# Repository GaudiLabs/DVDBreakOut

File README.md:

# DVDBreakOut
Simple breakout board to controll the laser and the two coils of an Optical Laser Pickup Unit

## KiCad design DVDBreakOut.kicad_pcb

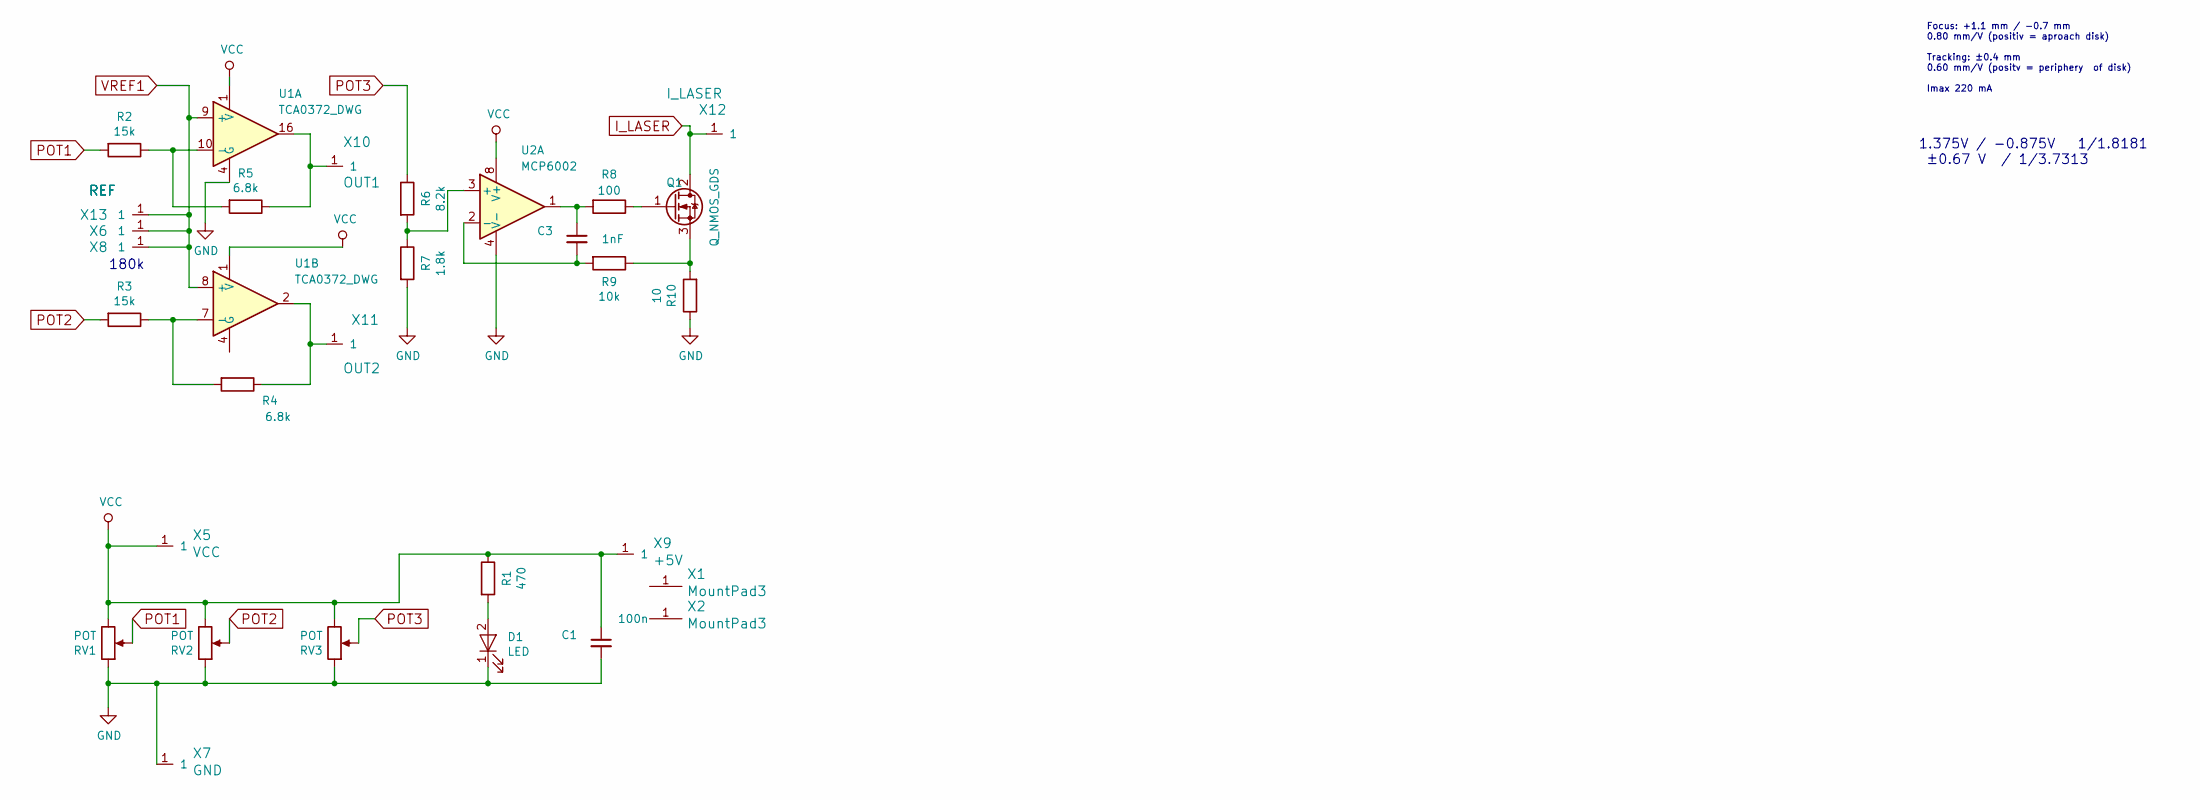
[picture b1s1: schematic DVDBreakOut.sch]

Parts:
C1: 100n; C_0805
C3: 1nF; C_0805
D1: LED; C_0805
Q1: Q_NMOS_GDS; TO-252-2Lead
R1: 470; C_0805
R2, R3: 15k; C_0805
R4, R5: 6.8k; C_0805
R6: 8.2k; C_0805
R7: 1.8k; C_0805
R8: 100; C_0805
R9: 10k; C_0805
R10: 10; C_0805
RV1, RV2, RV3: POT; POT_OvalPads
U1: TCA0372_DWG; SO-16-W
U2: MCP6002; SOIC-08_N
X1, X2: MountPad3; MountingHoleM3
X5: VCC; PAD_SMD_3mm
X6, X8, X13: REF; PAD_SMD_3mm
X7: GND; PAD_SMD_3mm
X9: +5V; PAD_SMD_3mm
X10: OUT1; PAD_SMD_3mm
X11: OUT2; PAD_SMD_3mm
X12: I_LASER; PAD_SMD_3mm

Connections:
GND: C1.2, D1.1 (K), R7.2, R10.1, RV1.1, RV2.1, RV3.1, U1.4 (G), U1.5 (GND), U1.12 (GND), U1.13 (GND), U2.4 (V-), X7.1
I_LASER: Q1.2 (D), X12.1
unnamed: C3.1, R8.2, U2.1
unnamed: C3.2, R9.2, U2.2 (-)
unnamed: D1.2 (A), R1.2
unnamed: Q1.1 (G), R8.1
unnamed: Q1.3 (S), R9.1, R10.2
unnamed: R2.1, R5.2, U1.10 (-)
unnamed: R3.1, R4.2, U1.7 (-)
unnamed: R4.1, U1.2, X11.1
unnamed: R5.1, U1.16, X10.1
unnamed: R6.2, R7.1, U2.3 (+)
POT1: R2.2, RV1.2
POT2: R3.2, RV2.2
POT3: R6.1, RV3.2
VCC: C1.1, R1.1, RV1.3, RV2.3, RV3.3, U1.1 (V), U2.8 (V+), X5.1, X9.1
VREF1: U1.8 (+), U1.9 (+), X6.1, X8.1, X13.1

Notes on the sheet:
Focus: +1.1 mm / -0.7 mm 0.80 mm/V (positiv = aproach disk) Tracking: ±0.4 mm 0.60 mm/V (positv = periphery of disk) Imax 220 mA
1.375V / -0.875V 1/1.8181 ±0.67 V / 1/3.7313
180k

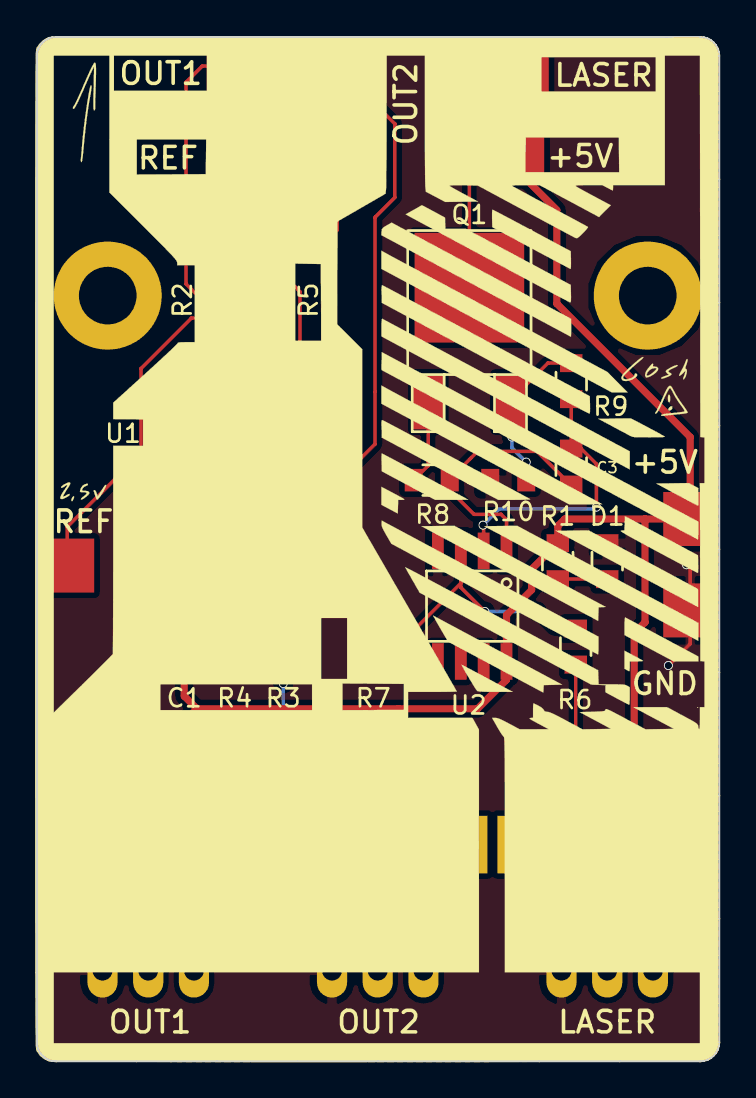
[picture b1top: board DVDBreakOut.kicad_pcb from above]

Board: 2 copper layers, 37.9 x 56.9 mm, 30 parts (0 on the bottom side), 17 nets.

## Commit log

2018-10-31 First upload board tested and working
